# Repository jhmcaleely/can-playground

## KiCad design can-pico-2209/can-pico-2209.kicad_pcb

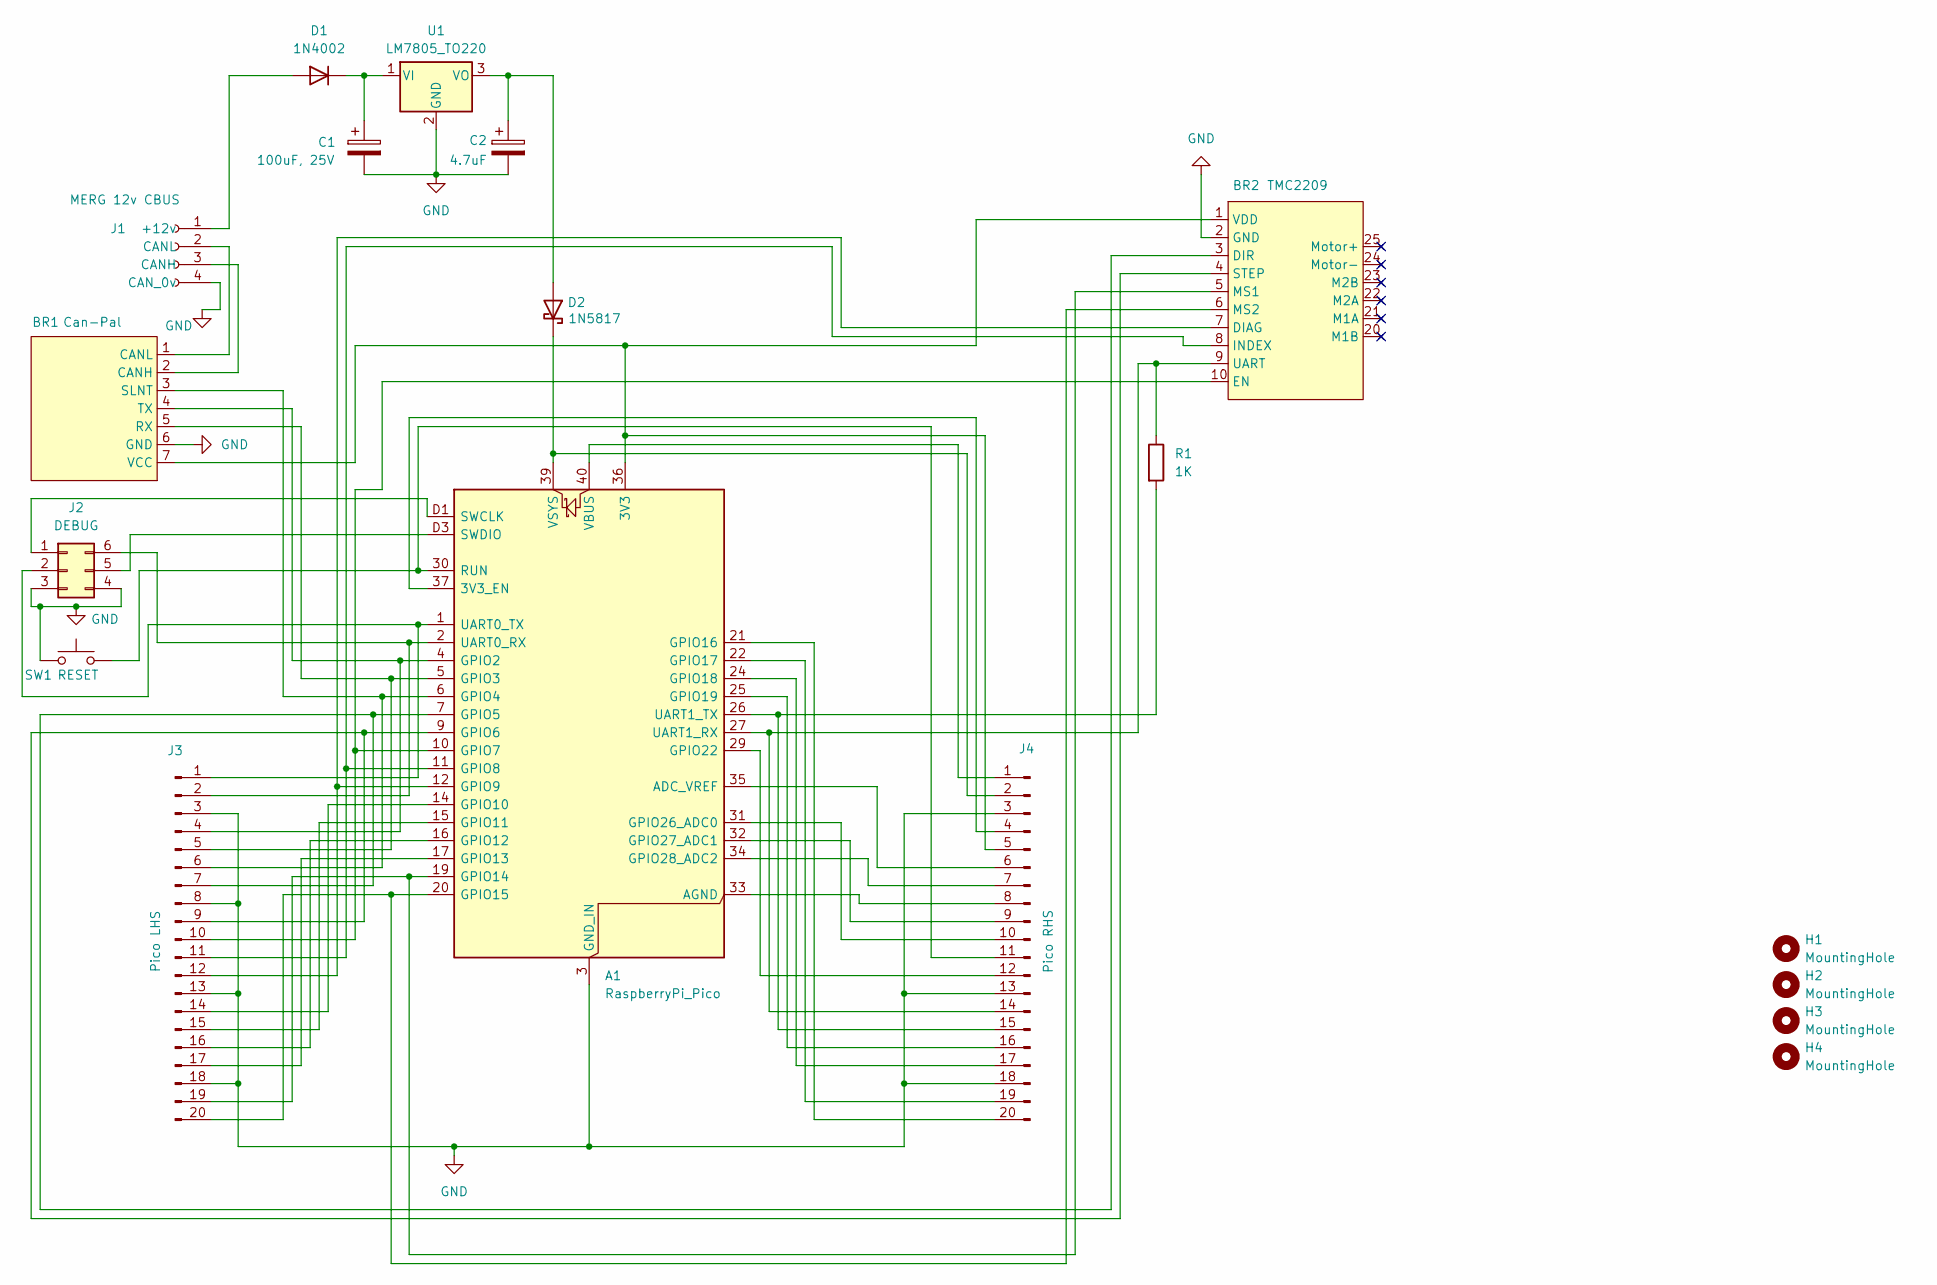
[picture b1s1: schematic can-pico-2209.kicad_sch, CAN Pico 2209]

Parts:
A1: RaspberryPi_Pico; RaspberryPi_Pico_SMD_HandSolder
BR1: Can-Pal; CAN-Pal
BR2: TMC2209; Adafruit 2209
C1: 100uF, 25V; CP_Radial_D4.0mm_P2.00mm
C2: 4.7uF; CP_Radial_Tantal_D4.5mm_P2.50mm
D1: 1N4002; D_DO-41_SOD81_P10.16mm_Horizontal
D2: 1N5817; D_DO-41_SOD81_P10.16mm_Horizontal
H1, H2, H3, H4: MountingHole; MountingHole_3.2mm_M3_Pad
J1: MERG 12v CBUS; TerminalBlock_Phoenix_PT-1,5-4-3.5-H_1x04_P3.50mm_Horizontal
J2: DEBUG; PinHeader_2x03_P2.54mm_Vertical
J3: Pico LHS; PinHeader_1x20_P2.54mm_Vertical
J4: Pico RHS; PinHeader_1x20_P2.54mm_Vertical
R1: 1K; R_Axial_DIN0207_L6.3mm_D2.5mm_P10.16mm_Horizontal
SW1: RESET; SW_PUSH_6mm
U1: LM7805_TO220; TO-220-3_Vertical

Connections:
GND: A1.3 (GND_IN), A1.8 (GND), A1.13 (GND), A1.18 (GND), A1.23 (GND), A1.28 (GND), A1.38 (GND), A1.D2 (GND), BR1.6 (GND), BR2.2 (GND), C1.2, C2.2, J1.4 (CAN_0v), J2.3, J2.4, J3.3, J3.8, J3.13, J3.18, J4.3, J4.13, J4.18, SW1.1, U1.2 (GND)
unnamed: A1.36 (3V3), BR1.7 (VCC), BR2.1 (VDD), J4.5
unnamed: A1.37 (3V3_EN), J4.4
unnamed: A1.35 (ADC_VREF), J4.6
unnamed: A1.33 (AGND), J4.8
unnamed: A1.1 (UART0_TX), J2.2, J3.1
unnamed: A1.2 (UART0_RX), J2.6, J3.2
unnamed: A1.4 (GPIO2), BR1.4 (TX), J3.4
unnamed: A1.5 (GPIO3), BR1.5 (RX), J3.5
unnamed: A1.6 (GPIO4), BR1.3 (SLNT), J3.6
unnamed: A1.7 (GPIO5), BR2.3 (DIR), J3.7
unnamed: A1.9 (GPIO6), BR2.4 (STEP), J3.9
unnamed: A1.10 (GPIO7), BR2.10 (EN), J3.10
unnamed: A1.11 (GPIO8), BR2.8 (INDEX), J3.11
unnamed: A1.12 (GPIO9), BR2.7 (DIAG), J3.12
unnamed: A1.14 (GPIO10), J3.14
unnamed: A1.15 (GPIO11), J3.15
unnamed: A1.16 (GPIO12), J3.16
unnamed: A1.17 (GPIO13), J3.17
unnamed: A1.19 (GPIO14), BR2.5 (MS1), J3.19
unnamed: A1.20 (GPIO15), BR2.6 (MS2), J3.20
unnamed: A1.21 (GPIO16), J4.20
unnamed: A1.22 (GPIO17), J4.19
unnamed: A1.24 (GPIO18), J4.17
unnamed: A1.25 (GPIO19), J4.16
unnamed: A1.26 (UART1_TX), J4.15, R1.2
unnamed: A1.27 (UART1_RX), BR2.9 (UART), J4.14, R1.1
unnamed: A1.29 (GPIO22), J4.12
unnamed: A1.31 (GPIO26_ADC0), J4.10
unnamed: A1.32 (GPIO27_ADC1), J4.9
unnamed: A1.34 (GPIO28_ADC2), J4.7
unnamed: A1.30 (RUN), J4.11, SW1.2
unnamed: A1.D1 (SWCLK), J2.1
unnamed: A1.D3 (SWDIO), J2.5
unnamed: A1.40 (VBUS), J4.1 (VBUS)
unnamed: A1.39 (VSYS), D2.1 (K), J4.2
unnamed: BR1.2 (CANH), J1.3 (CANH)
unnamed: BR1.1 (CANL), J1.2 (CANL)
unnamed: D1.2 (A), J1.1 (+12v)
unnamed: C1.1, D1.1 (K), U1.1 (VI)
unnamed: C2.1, D2.2 (A), U1.3 (VO)

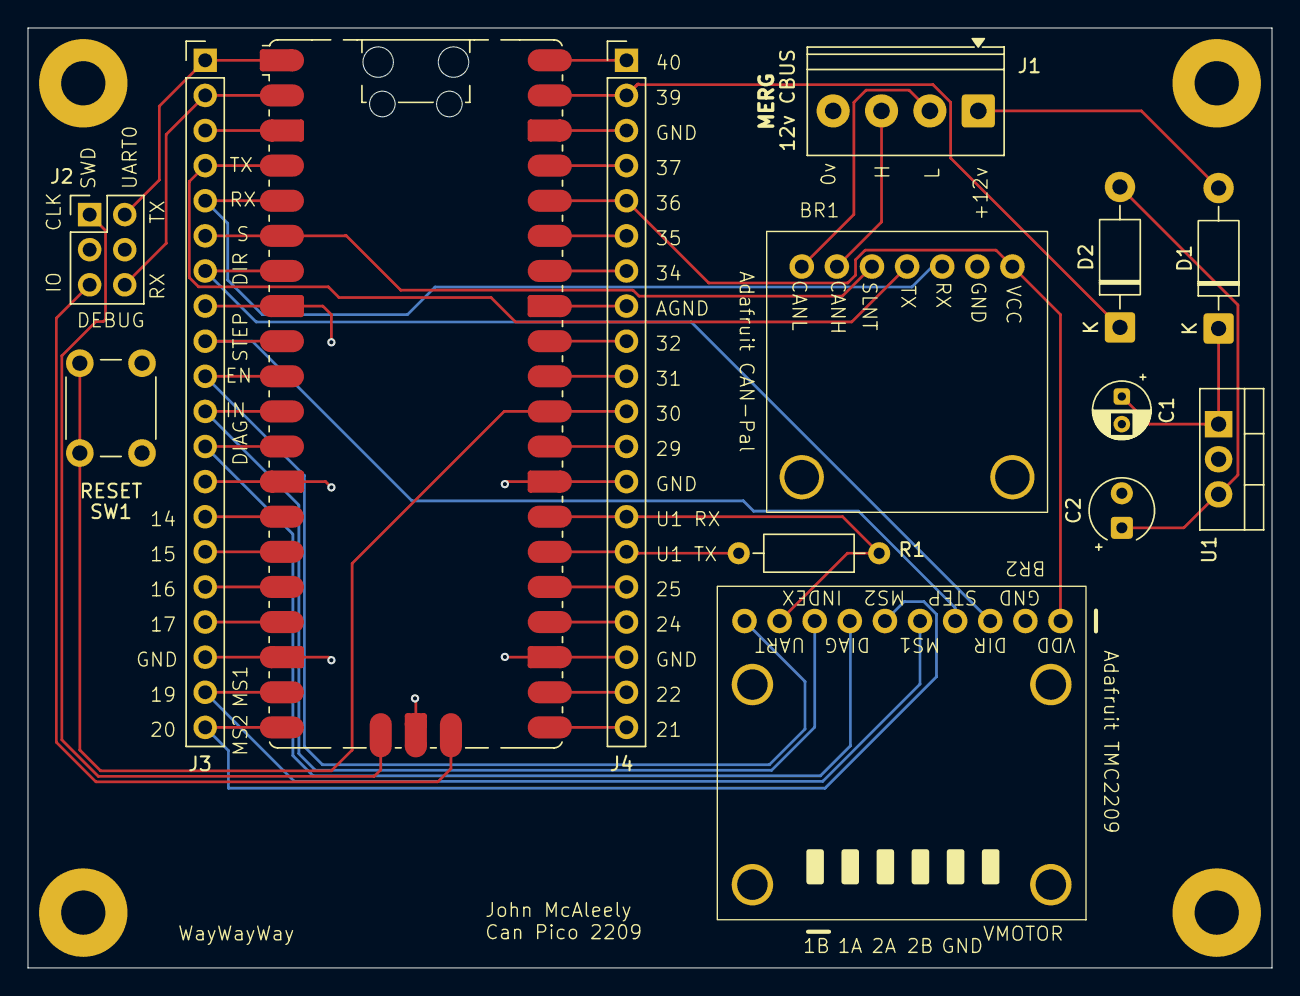
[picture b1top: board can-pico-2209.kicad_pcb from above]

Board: 2 copper layers, 90.0 x 68.0 mm, 18 parts (0 on the bottom side), 41 nets.
